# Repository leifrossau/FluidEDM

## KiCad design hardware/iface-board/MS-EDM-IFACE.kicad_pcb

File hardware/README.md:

# Microspark EDM — Hardware (KiCad 10)

KiCad 10 projects for the two boards the firmware talks to over CAN-FD but that did not yet
exist: the **dielectric (coolant) controller** and the **EDM pulse supply (PSU)**. Both were
generated programmatically with KiCad 10's headless `pcbnew` Python API + `kicad-cli`.

> **These are AI-generated first-pass designs, NOT fabrication-ready.** Read each board's
> `DESIGN.md` (every significant choice is flagged **[REVIEW]**). The PSU board is high-voltage
> and **must not be fabricated or powered without a qualified power-electronics review,
> simulation, and staged bench bring-up** — see `psu-board/DESIGN.md`.

## Layout
```
hardware/
  dielectric-module/   MS-DIEL-CTRL — ESP32-S3 + MCP2518FD CAN node, coolant sensors/drives
  psu-board/           MS-EDM-PSU   — STM32G474 HV pulse generator + classifier (review-only)
  lib/                 (project-local symbols/footprints, if any)
  scripts/kizen.py     shared headless board-builder helper
```
Each board dir has: `DESIGN.md` (the engineering), `generate_board.py` (regenerates the PCB),
`*.kicad_pro/.kicad_pcb` (the KiCad project — open in **KiCad 10**, not 9), `*.netlist.csv`
(pad→net review table), `*.bom.csv`, and `*.placement.pdf` (a rendered view).

## Workflow: schematic-first (linked)
The **dielectric board** is generated schematic-first (option A): one shared source model
(`generate.py`, the `PARTS` + `NETS` tables) emits BOTH the `.kicad_sch` (source of truth)
and the `.kicad_pcb`, with each footprint carrying the **same UUID** as its schematic symbol —
so the two are linked and "Update PCB from Schematic" / ERC are meaningful. ICs are wired by
**pin name** resolved against the real library symbol (authoritative pinouts, e.g. MCP2518FD
SCK=10/SDI=11/SDO=12/CS=13), the ESP32 by GPIO name. Connectivity in the schematic is
**global-label-per-pin** — ERC-valid and netlist-correct, but a flat "label wall", not a
hand-drawn schematic; prettify wiring in eeschema if desired. The toolkit is `scripts/kisch.py`
(schematic) + `scripts/kizen.py` (PCB). The **PSU board** is still the earlier PCB-only scaffold.

## What is done vs. what's left
**Done (autonomously):** architecture + part selection, a **linked schematic + PCB** (dielectric),
real-symbol pinouts, board outline, block placement, complete netlist/ratsnest, copper-pour
outlines, mounting, ERC + DRC + schematic/PCB PDFs, BOM.

**Left (needs the KiCad GUI / a human):**
- **Routing** — nothing is routed (the ratsnest shows all connections). DRC's "unconnected" count is expected.
- **ERC nags** — the generated schematic leaves benign warnings: unused-GPIO `pin_not_connected`
  (add no-connect flags), `power_pin_not_driven` (add `PWR_FLAG`s), and `lib_symbol_mismatch`
  (the embedded symbols differ slightly from the library cache — "Update Symbols from Library").
- **Placement polish** — remaining DRC items are mostly silkscreen-label overlaps + courtyard
  nudges + default drill-rule flags on the big mount/terminal holes; resolve while routing.
- **A few [REVIEW] part choices** — buck `AP3402`, reverse-FET `AO3401A`, and the programming
  header replacing USB-C (pad-mapping); confirm against the BOM you intend to buy.
- **Pour fill** — zones are left unfilled (headless `ZONE_FILLER` segfaults); press **B** in pcbnew.

## Regenerate a board
```powershell
& "C:\Program Files\KiCad\10.0\bin\python.exe" hardware\dielectric-module\generate.py        # schematic + linked PCB
& "C:\Program Files\KiCad\10.0\bin\python.exe" hardware\psu-board\generate_board.py           # PCB scaffold only
```
Render / check (kicad-cli):
```powershell
$cli = "C:\Program Files\KiCad\10.0\bin\kicad-cli.exe"
& $cli pcb export pdf  --layers "F.Cu,F.Silkscreen,F.Fab,Edge.Cuts" --mode-single <board>.kicad_pcb
& $cli pcb drc --format json --output drc.json <board>.kicad_pcb
```
The generators are **idempotent** — re-running rebuilds the `.kicad_pcb` from the component +
net tables in `generate_board.py`. Edit those tables (or `scripts/kizen.py`) to change the board;
re-run to regenerate. (Once you start hand-editing/routing in the GUI, stop re-running the
generator or it will overwrite your work — at that point the `.kicad_pcb` is the source of truth.)

## Firmware contracts these implement
- **Dielectric:** CAN IDs `0x710–0x740` — `docs/superpowers/specs/2026-06-14-dielectric-module-design.md`.
- **PSU:** CAN IDs `0x010/0x020/0x100/0x300` — the PSU integration design spec.
Both boards' MCUs run separate firmware (not in this repo yet); the contracts + the firmware's
`SimPsuLink`/`SimDielLink` simulators let you validate the bus handshake before either board exists.

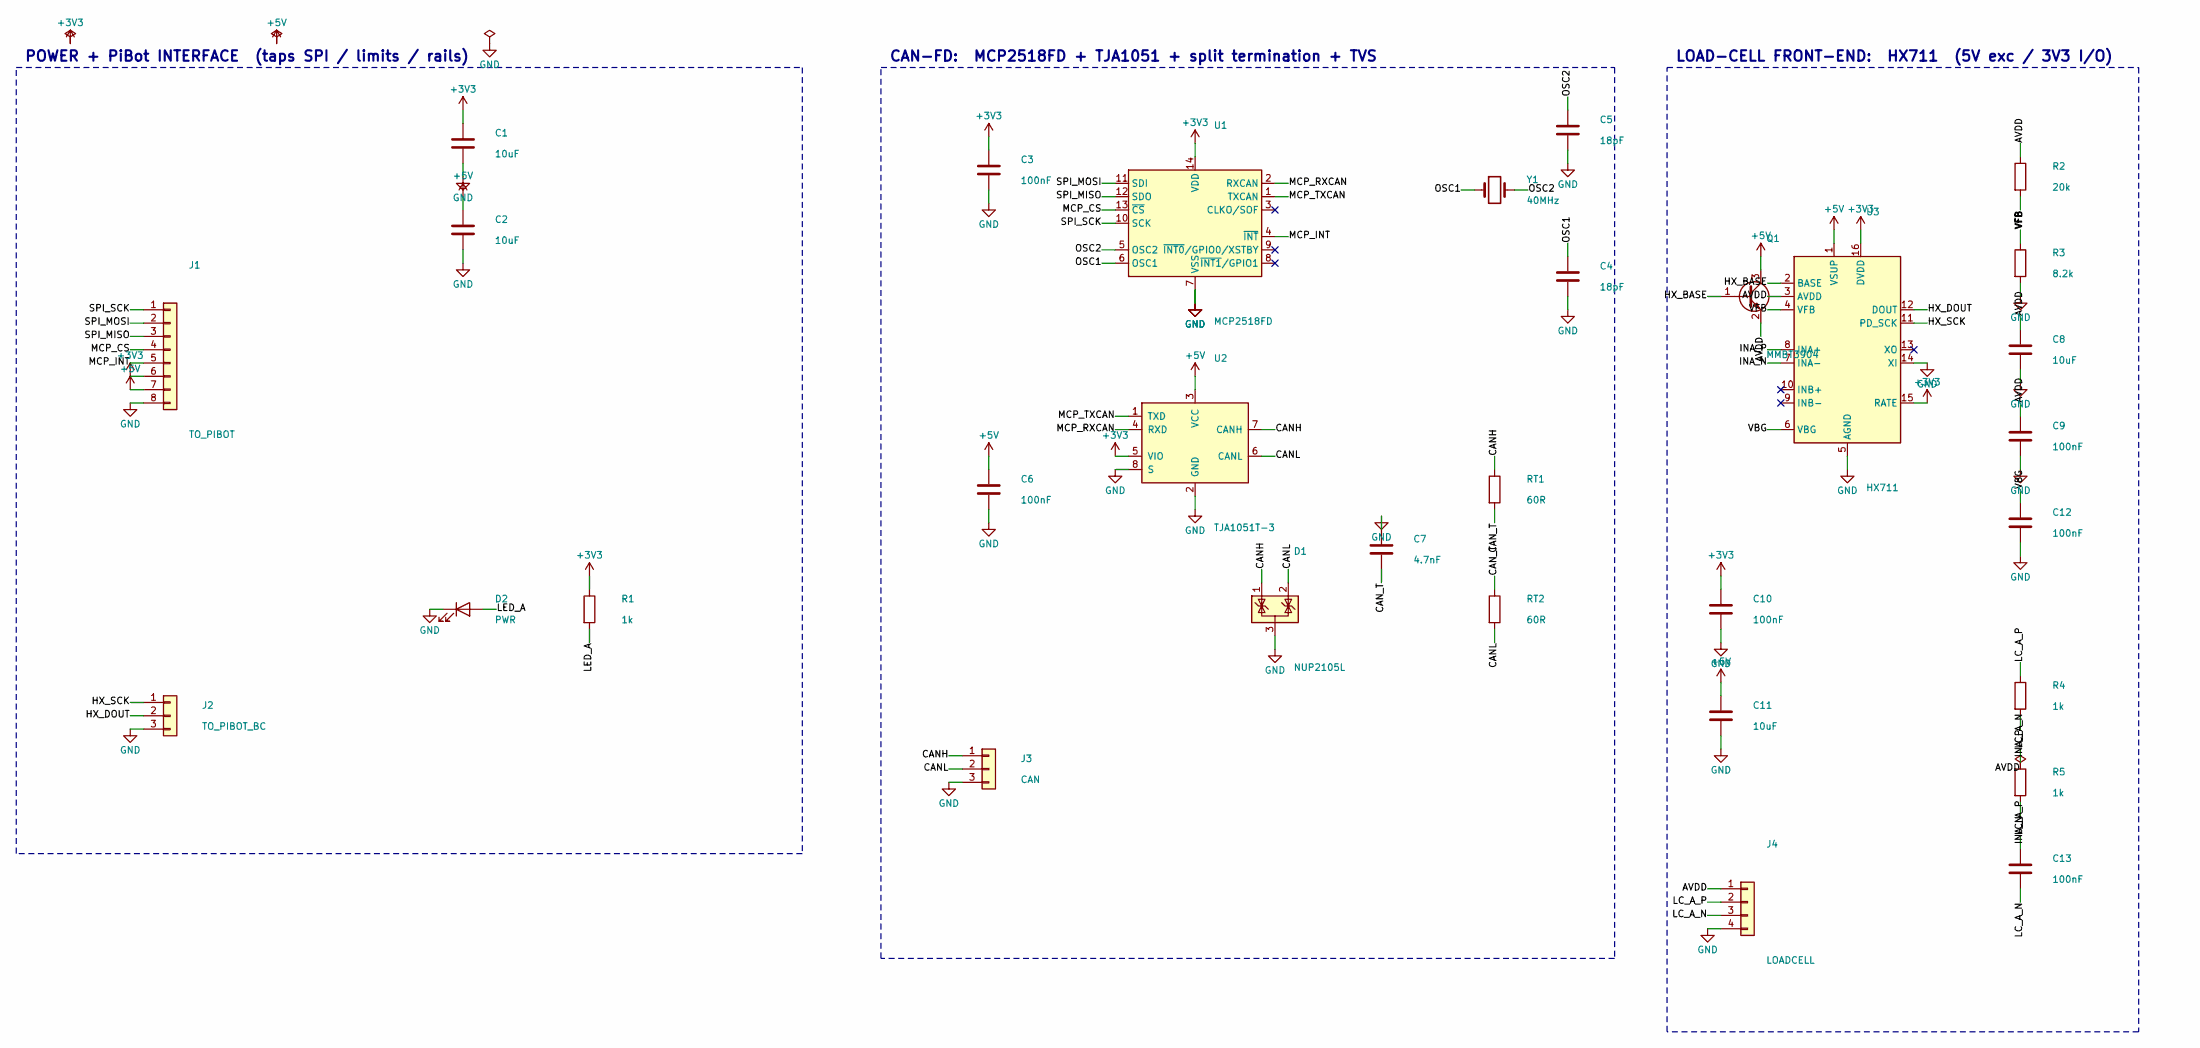
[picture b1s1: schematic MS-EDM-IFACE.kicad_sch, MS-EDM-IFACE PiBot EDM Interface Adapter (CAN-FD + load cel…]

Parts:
C1, C2, C8, C11: 10uF; C_0805_2012Metric
C3, C6, C9, C10, C12, C13: 100nF; C_0805_2012Metric
C4, C5: 18pF; C_0805_2012Metric
C7: 4.7nF; C_0805_2012Metric
D1: NUP2105L; SOT-23
D2: PWR; LED_0805_2012Metric
J1: TO_PIBOT; PinHeader_1x08_P2.54mm_Vertical
J2: TO_PIBOT_BC; PinHeader_1x03_P2.54mm_Vertical
J3: CAN; TerminalBlock_Phoenix_MPT-0,5-3-2.54_1x03_P2.54mm_Horizontal
J4: LOADCELL; JST_XH_B4B-XH-A_1x04_P2.50mm_Vertical
Q1: MMBT3904; SOT-23
R1, R4, R5: 1k; R_0805_2012Metric
R2: 20k; R_0805_2012Metric
R3: 8.2k; R_0805_2012Metric
RT1, RT2: 60R; R_0805_2012Metric
U1: MCP2518FD; SOIC-14_3.9x8.7mm_P1.27mm
U2: TJA1051T-3; SOIC-8_3.9x4.9mm_P1.27mm
U3: HX711; SOIC-16_3.9x9.9mm_P1.27mm
Y1: 40MHz; Crystal_SMD_3215-2Pin_3.2x1.5mm

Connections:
+3V3: C1.1, C3.1, C10.1, J1.6, R1.1, U1.14 (VDD), U2.5 (VIO), U3.15 (RATE), U3.16 (DVDD)
+5V: C2.1, C6.1, C11.1, J1.7, Q1.3 (C), U2.3 (VCC), U3.1 (VSUP)
AVDD: C8.1, C9.1, J4.1, Q1.2 (E), R2.1, U3.3 (AVDD)
CANH: D1.1 (K), J3.1, RT1.1, U2.7 (CANH)
CANL: D1.2 (K), J3.2, RT2.2, U2.6 (CANL)
CAN_T: C7.2, RT1.2, RT2.1
GND: C1.2, C2.2, C3.2, C4.2, C5.2, C6.2, C7.1, C8.2, C9.2, C10.2, C11.2, C12.2, D1.3 (A), D2.1 (K), J1.8, J2.3, J3.3, J4.4, R3.2, U1.7 (VSS), U1.15 (VSS), U2.2 (GND), U2.8 (S), U3.5 (AGND), U3.14 (XI)
HX_BASE: Q1.1 (B), U3.2 (BASE)
HX_DOUT: J2.2, U3.12 (DOUT)
HX_SCK: J2.1, U3.11 (PD_SCK)
INA_N: R5.2, U3.7 (INA-)
INA_P: R4.2, U3.8 (INA+)
LC_A_N: C13.2, J4.3, R5.1
LC_A_P: C13.1, J4.2, R4.1
LED_A: D2.2 (A), R1.2
MCP_CS: J1.4, U1.13 (~CS)
MCP_INT: J1.5, U1.4 (~INT)
MCP_RXCAN: U1.2 (RXCAN), U2.4 (RXD)
MCP_TXCAN: U1.1 (TXCAN), U2.1 (TXD)
OSC1: C4.1, U1.6 (OSC1), Y1.1
OSC2: C5.1, U1.5 (OSC2), Y1.2
SPI_MISO: J1.3, U1.12 (SDO)
SPI_MOSI: J1.2, U1.11 (SDI)
SPI_SCK: J1.1, U1.10 (SCK)
VBG: C12.1, U3.6 (VBG)
VFB: R2.2, R3.1, U3.4 (VFB)

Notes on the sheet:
POWER + PiBot INTERFACE (taps SPI / limits / rails)
CAN-FD: MCP2518FD + TJA1051 + split termination + TVS
LOAD-CELL FRONT-END: HX711 (5V exc / 3V3 I/O)

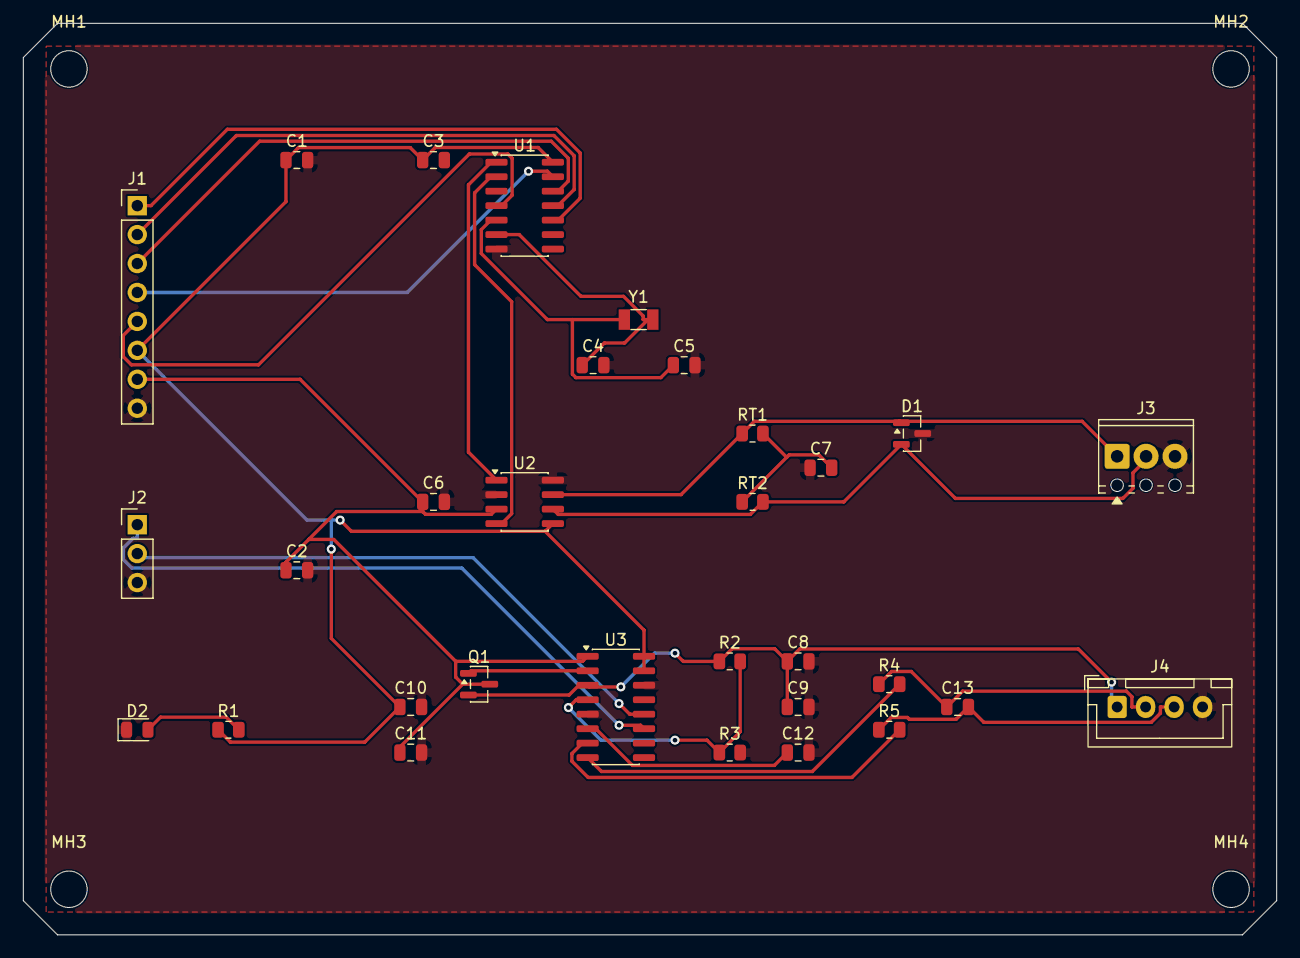
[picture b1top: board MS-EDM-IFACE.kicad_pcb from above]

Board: 2 copper layers, 110.0 x 80.0 mm, 35 parts (0 on the bottom side), 26 nets.

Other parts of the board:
MH1, MH2, MH3, MH4: M3; MountingHole_3.2mm_M3

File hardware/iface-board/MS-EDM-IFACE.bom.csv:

qty,value,footprint,refs
6,100nF,C_0805_2012Metric,C10 C12 C13 C3 C6 C9
4,10uF,C_0805_2012Metric,C1 C11 C2 C8
2,18pF,C_0805_2012Metric,C4 C5
3,1k,R_0805_2012Metric,R1 R4 R5
1,20k,R_0805_2012Metric,R2
1,4.7nF,C_0805_2012Metric,C7
1,40MHz,Crystal_SMD_3215-2Pin_3.2x1.5mm,Y1
2,60R,R_0805_2012Metric,RT1 RT2
1,8.2k,R_0805_2012Metric,R3
1,CAN,"TerminalBlock_Phoenix_MPT-0,5-3-2.54_1x03_P2.54mm_Horizontal",J3
1,HX711,SOIC-16_3.9x9.9mm_P1.27mm,U3
1,LOADCELL,JST_XH_B4B-XH-A_1x04_P2.50mm_Vertical,J4
4,M3,MountingHole_3.2mm_M3,MH1 MH2 MH3 MH4
1,MCP2518FD,SOIC-14_3.9x8.7mm_P1.27mm,U1
1,MMBT3904,SOT-23,Q1
1,NUP2105L,SOT-23,D1
1,PWR,LED_0805_2012Metric,D2
1,TJA1051T-3,SOIC-8_3.9x4.9mm_P1.27mm,U2
1,TO_PIBOT,PinHeader_1x08_P2.54mm_Vertical,J1
1,TO_PIBOT_BC,PinHeader_1x03_P2.54mm_Vertical,J2

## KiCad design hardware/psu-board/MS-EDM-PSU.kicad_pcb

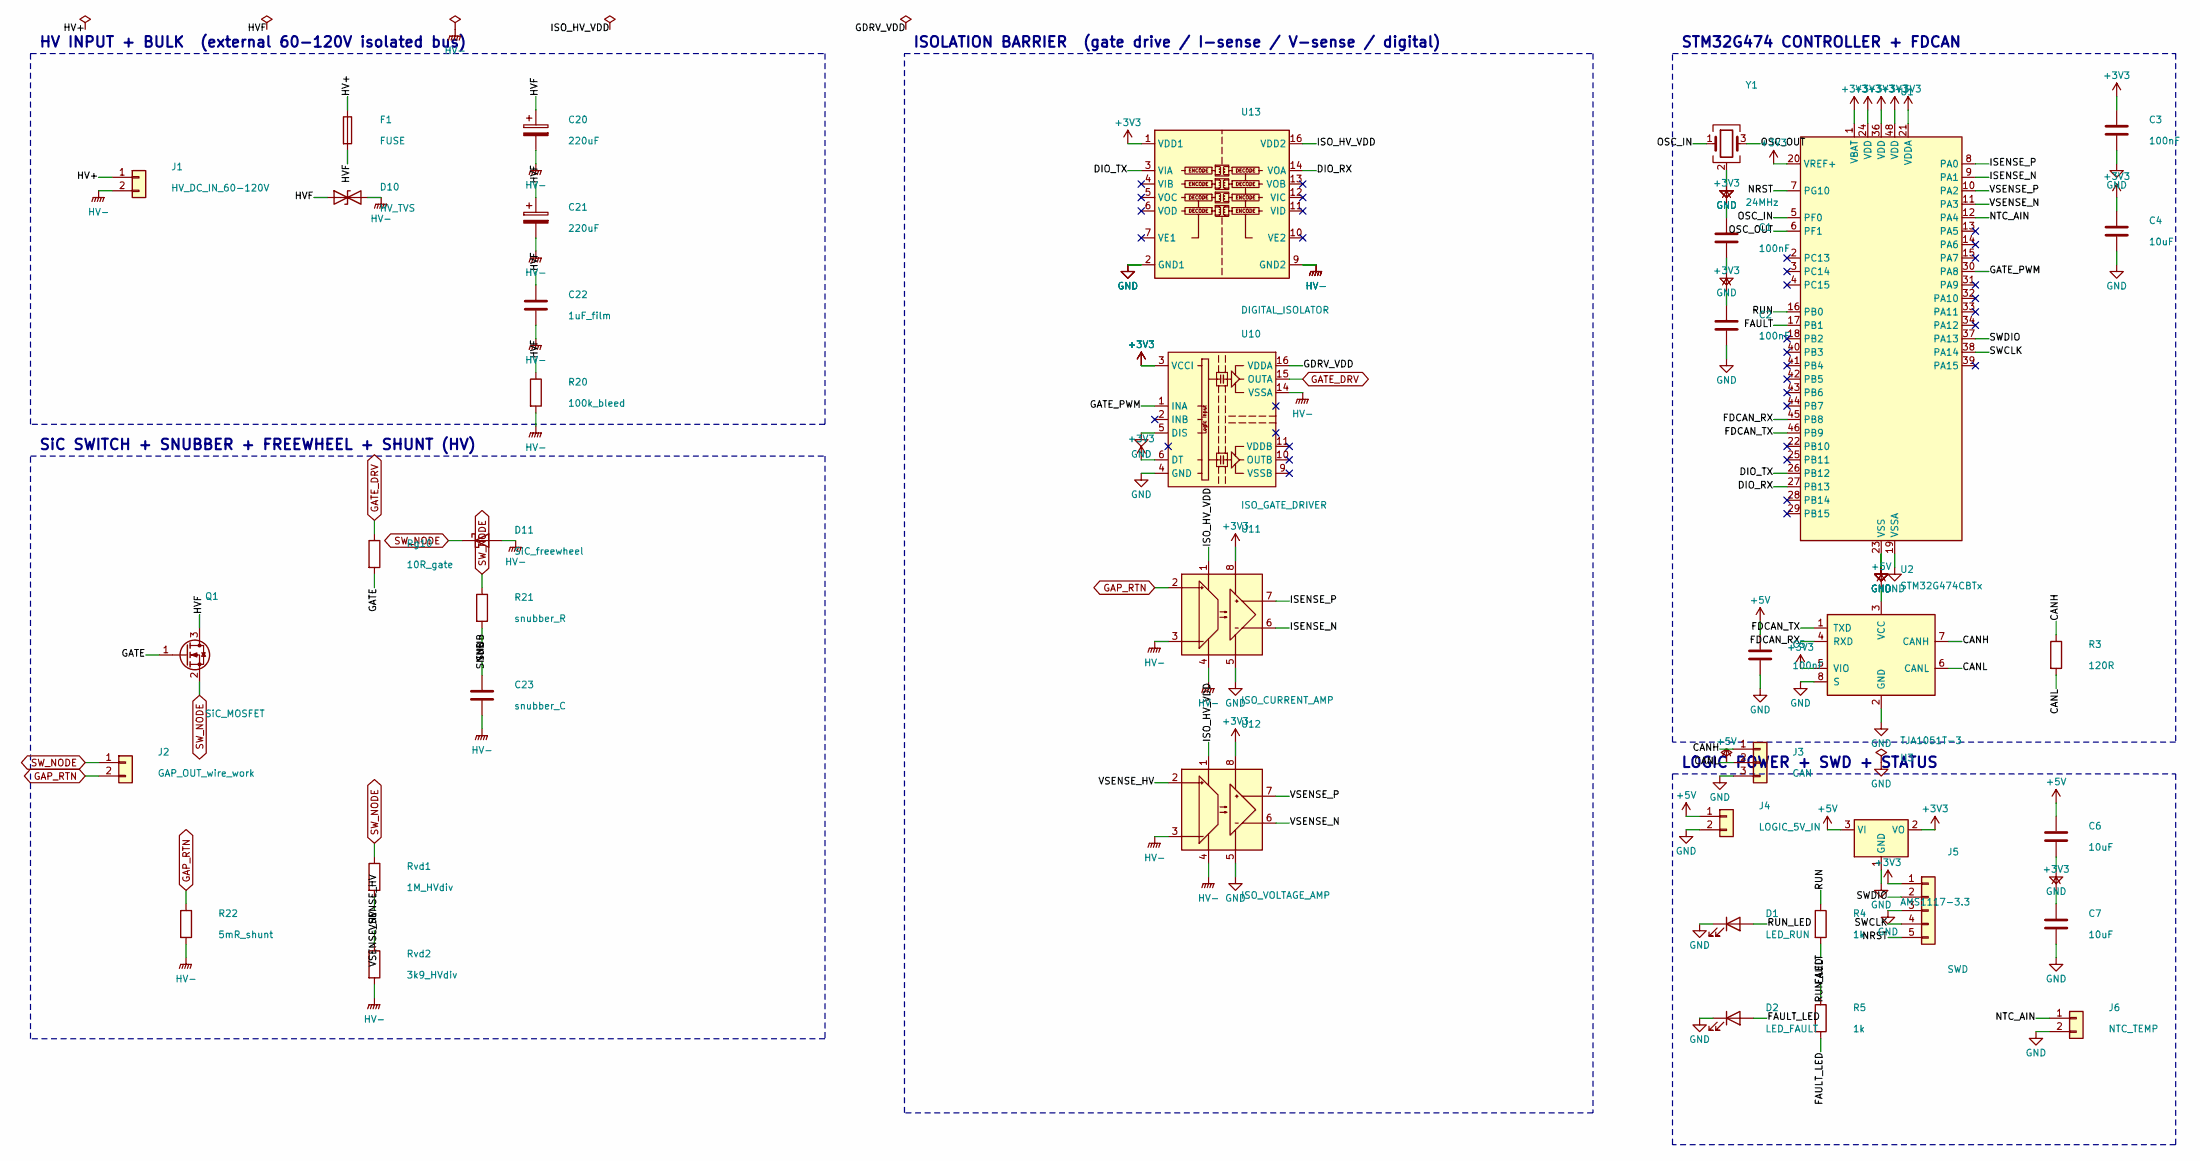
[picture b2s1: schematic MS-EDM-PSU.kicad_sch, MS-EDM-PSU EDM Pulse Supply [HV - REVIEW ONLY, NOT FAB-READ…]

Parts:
C1, C2, C3, C5: 100nF; C_0805_2012Metric
C4, C6, C7: 10uF; C_0805_2012Metric
C20, C21: 220uF; CP_Radial_D10.0mm_P5.00mm
C22: 1uF_film; C_1210_3225Metric
C23: snubber_C; C_0805_2012Metric
D1: LED_RUN; LED_0805_2012Metric
D2: LED_FAULT; LED_0805_2012Metric
D10: HV_TVS; D_SMC
D11: SiC_freewheel; D_SMC
F1: FUSE; R_2512_6332Metric
J1: HV_DC_IN_60-120V; TerminalBlock_Phoenix_MPT-0,5-2-2.54_1x02_P2.54mm_Horizontal
J2: GAP_OUT_wire_work; TerminalBlock_Phoenix_MPT-0,5-2-2.54_1x02_P2.54mm_Horizontal
J3: CAN; TerminalBlock_Phoenix_MPT-0,5-3-2.54_1x03_P2.54mm_Horizontal
J4: LOGIC_5V_IN; TerminalBlock_Phoenix_MPT-0,5-2-2.54_1x02_P2.54mm_Horizontal
J5: SWD; PinHeader_1x05_P2.54mm_Vertical
J6: NTC_TEMP; TerminalBlock_Phoenix_MPT-0,5-2-2.54_1x02_P2.54mm_Horizontal
Q1: SiC_MOSFET; TO-247-3_Vertical
R3: 120R; R_0805_2012Metric
R4, R5: 1k; R_0805_2012Metric
R20: 100k_bleed; R_2512_6332Metric
R21: snubber_R; R_2512_6332Metric
R22: 5mR_shunt; R_2512_6332Metric
Rg10: 10R_gate; R_0805_2012Metric
Rvd1: 1M_HVdiv; R_2512_6332Metric
Rvd2: 3k9_HVdiv; R_0805_2012Metric
U1: STM32G474CBTx; LQFP-48_7x7mm_P0.5mm
U2: TJA1051T-3; SOIC-8_3.9x4.9mm_P1.27mm
U3: AMS1117-3.3; SOT-223-3_TabPin2
U10: ISO_GATE_DRIVER; SOIC-16W_7.5x10.3mm_P1.27mm
U11: ISO_CURRENT_AMP; SOIC-8_3.9x4.9mm_P1.27mm
U12: ISO_VOLTAGE_AMP; SOIC-8_3.9x4.9mm_P1.27mm
U13: DIGITAL_ISOLATOR; SOIC-16_3.9x9.9mm_P1.27mm
Y1: 24MHz; Crystal_SMD_3225-4Pin_3.2x2.5mm

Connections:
+3V3: C1.1, C2.1, C3.1, C4.1, C7.1, J5.1, U1.1 (VBAT), U1.20 (VREF+), U1.21 (VDDA), U1.24 (VDD), U1.36 (VDD), U1.48 (VDD), U2.5 (VIO), U3.2 (VO), U10.3 (VCCI), U10.6 (DT), U10.8 (VCCI), U11.8 (VDD2), U12.8 (VDD2), U13.1 (VDD1)
CANH: J3.1, R3.1, U2.7 (CANH)
DIO_RX: U1.27 (PB13), U13.14 (VOA)
DIO_TX: U1.26 (PB12), U13.3 (VIA)
FAULT: R5.1, U1.17 (PB1)
FAULT_LED: D2.2 (A), R5.2
FDCAN_RX: U1.45 (PB8), U2.4 (RXD)
FDCAN_TX: U1.46 (PB9), U2.1 (TXD)
GAP_RTN: J2.2, R22.1, U11.2 (VINP)
GATE: Q1.1 (G), Rg10.2
GATE_DRV: Rg10.1, U10.15 (OUTA)
GATE_PWM: U1.30 (PA8), U10.1 (INA)
GDRV_VDD: U10.16 (VDDA)
GND: C1.2, C2.2, C3.2, C4.2, C5.2, C6.2, C7.2, D1.1 (K), D2.1 (K), J3.3, J4.2, J5.3, J6.2, U1.19 (VSSA), U1.23 (VSS), U1.35 (VSS), U1.47 (VSS), U2.2 (GND), U2.8 (S), U3.1 (GND), U10.4 (GND), U10.5 (DIS), U11.5 (GND2), U12.5 (GND2), U13.2 (GND1), U13.8 (GND1), Y1.2 (G), Y1.4 (G)
HV+: F1.1, J1.1
HV-: C20.2, C21.2, C22.2, C23.2, D10.2 (A2), D11.2 (A), J1.2, R20.2, R22.2, Rvd2.2, U10.14 (VSSA), U11.3 (VINN), U11.4 (GND1), U12.3 (VINN), U12.4 (GND1), U13.9 (GND2), U13.15 (GND2)
HVF: C20.1, C21.1, C22.1, D10.1 (A1), F1.2, Q1.3 (D), R20.1
ISENSE_N: U1.9 (PA1), U11.6 (VOUTN)
ISENSE_P: U1.8 (PA0), U11.7 (VOUTP)
ISO_HV_VDD: U11.1 (VDD1), U12.1 (VDD1), U13.16 (VDD2)
NRST: J5.5, U1.7 (PG10)
NTC_AIN: J6.1, U1.12 (PA4)
OSC_IN: U1.5 (PF0), Y1.1
OSC_OUT: U1.6 (PF1), Y1.3
RUN: R4.1, U1.16 (PB0)
RUN_LED: D1.2 (A), R4.2
SNUB: C23.1, R21.2
SWCLK: J5.4, U1.38 (PA14)
SWDIO: J5.2, U1.37 (PA13)
SW_NODE: D11.1 (K), J2.1, Q1.2 (S), R21.1, Rvd1.1
VSENSE_HV: Rvd1.2, Rvd2.1, U12.2 (VINP)
VSENSE_N: U1.11 (PA3), U12.6 (VOUTN)
VSENSE_P: U1.10 (PA2), U12.7 (VOUTP)

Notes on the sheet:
HV INPUT + BULK (external 60-120V isolated bus)
SiC SWITCH + SNUBBER + FREEWHEEL + SHUNT (HV)
ISOLATION BARRIER (gate drive / I-sense / V-sense / digital)
STM32G474 CONTROLLER + FDCAN
LOGIC POWER + SWD + STATUS

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
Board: 4 copper layers, 44 parts (0 on the bottom side), 34 nets, no tracks yet.

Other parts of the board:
MH1, MH2, MH3, MH4: M3; MountingHole_3.2mm_M3

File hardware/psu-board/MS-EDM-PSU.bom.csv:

qty,value,footprint,refs
1,100k_bleed,R_2512_6332Metric,R20
4,100nF,C_0805_2012Metric,C1 C2 C3 C5
1,10R_gate,R_0805_2012Metric,Rg10
3,10uF,C_0805_2012Metric,C4 C6 C7
1,120R,R_0805_2012Metric,R3
1,1M_HVdiv,R_2512_6332Metric,Rvd1
2,1k,R_0805_2012Metric,R4 R5
1,1uF_film,C_1210_3225Metric,C22
2,220uF,CP_Radial_D10.0mm_P5.00mm,C20 C21
1,24MHz,Crystal_SMD_3225-4Pin_3.2x2.5mm,Y1
1,3k9_HVdiv,R_0805_2012Metric,Rvd2
1,5mR_shunt,R_2512_6332Metric,R22
1,AMS1117-3.3,SOT-223-3_TabPin2,U3
1,CAN,"TerminalBlock_Phoenix_MPT-0,5-3-2.54_1x03_P2.54mm_Horizontal",J3
1,DIGITAL_ISOLATOR,SOIC-16_3.9x9.9mm_P1.27mm,U13
1,FUSE,R_2512_6332Metric,F1
1,GAP_OUT_wire_work,"TerminalBlock_Phoenix_MPT-0,5-2-2.54_1x02_P2.54mm_Horizontal",J2
1,HV_DC_IN_60-120V,"TerminalBlock_Phoenix_MPT-0,5-2-2.54_1x02_P2.54mm_Horizontal",J1
1,HV_TVS,D_SMC,D10
1,ISO_CURRENT_AMP,SOIC-8_3.9x4.9mm_P1.27mm,U11
1,ISO_GATE_DRIVER,SOIC-16W_7.5x10.3mm_P1.27mm,U10
1,ISO_VOLTAGE_AMP,SOIC-8_3.9x4.9mm_P1.27mm,U12
1,LED_FAULT,LED_0805_2012Metric,D2
1,LED_RUN,LED_0805_2012Metric,D1
1,LOGIC_5V_IN,"TerminalBlock_Phoenix_MPT-0,5-2-2.54_1x02_P2.54mm_Horizontal",J4
4,M3,MountingHole_3.2mm_M3,MH1 MH2 MH3 MH4
1,NTC_TEMP,"TerminalBlock_Phoenix_MPT-0,5-2-2.54_1x02_P2.54mm_Horizontal",J6
1,STM32G474CBTx,LQFP-48_7x7mm_P0.5mm,U1
1,SWD,PinHeader_1x05_P2.54mm_Vertical,J5
1,SiC_MOSFET,TO-247-3_Vertical,Q1
1,SiC_freewheel,D_SMC,D11
1,TJA1051T-3,SOIC-8_3.9x4.9mm_P1.27mm,U2
1,snubber_C,C_0805_2012Metric,C23
1,snubber_R,R_2512_6332Metric,R21

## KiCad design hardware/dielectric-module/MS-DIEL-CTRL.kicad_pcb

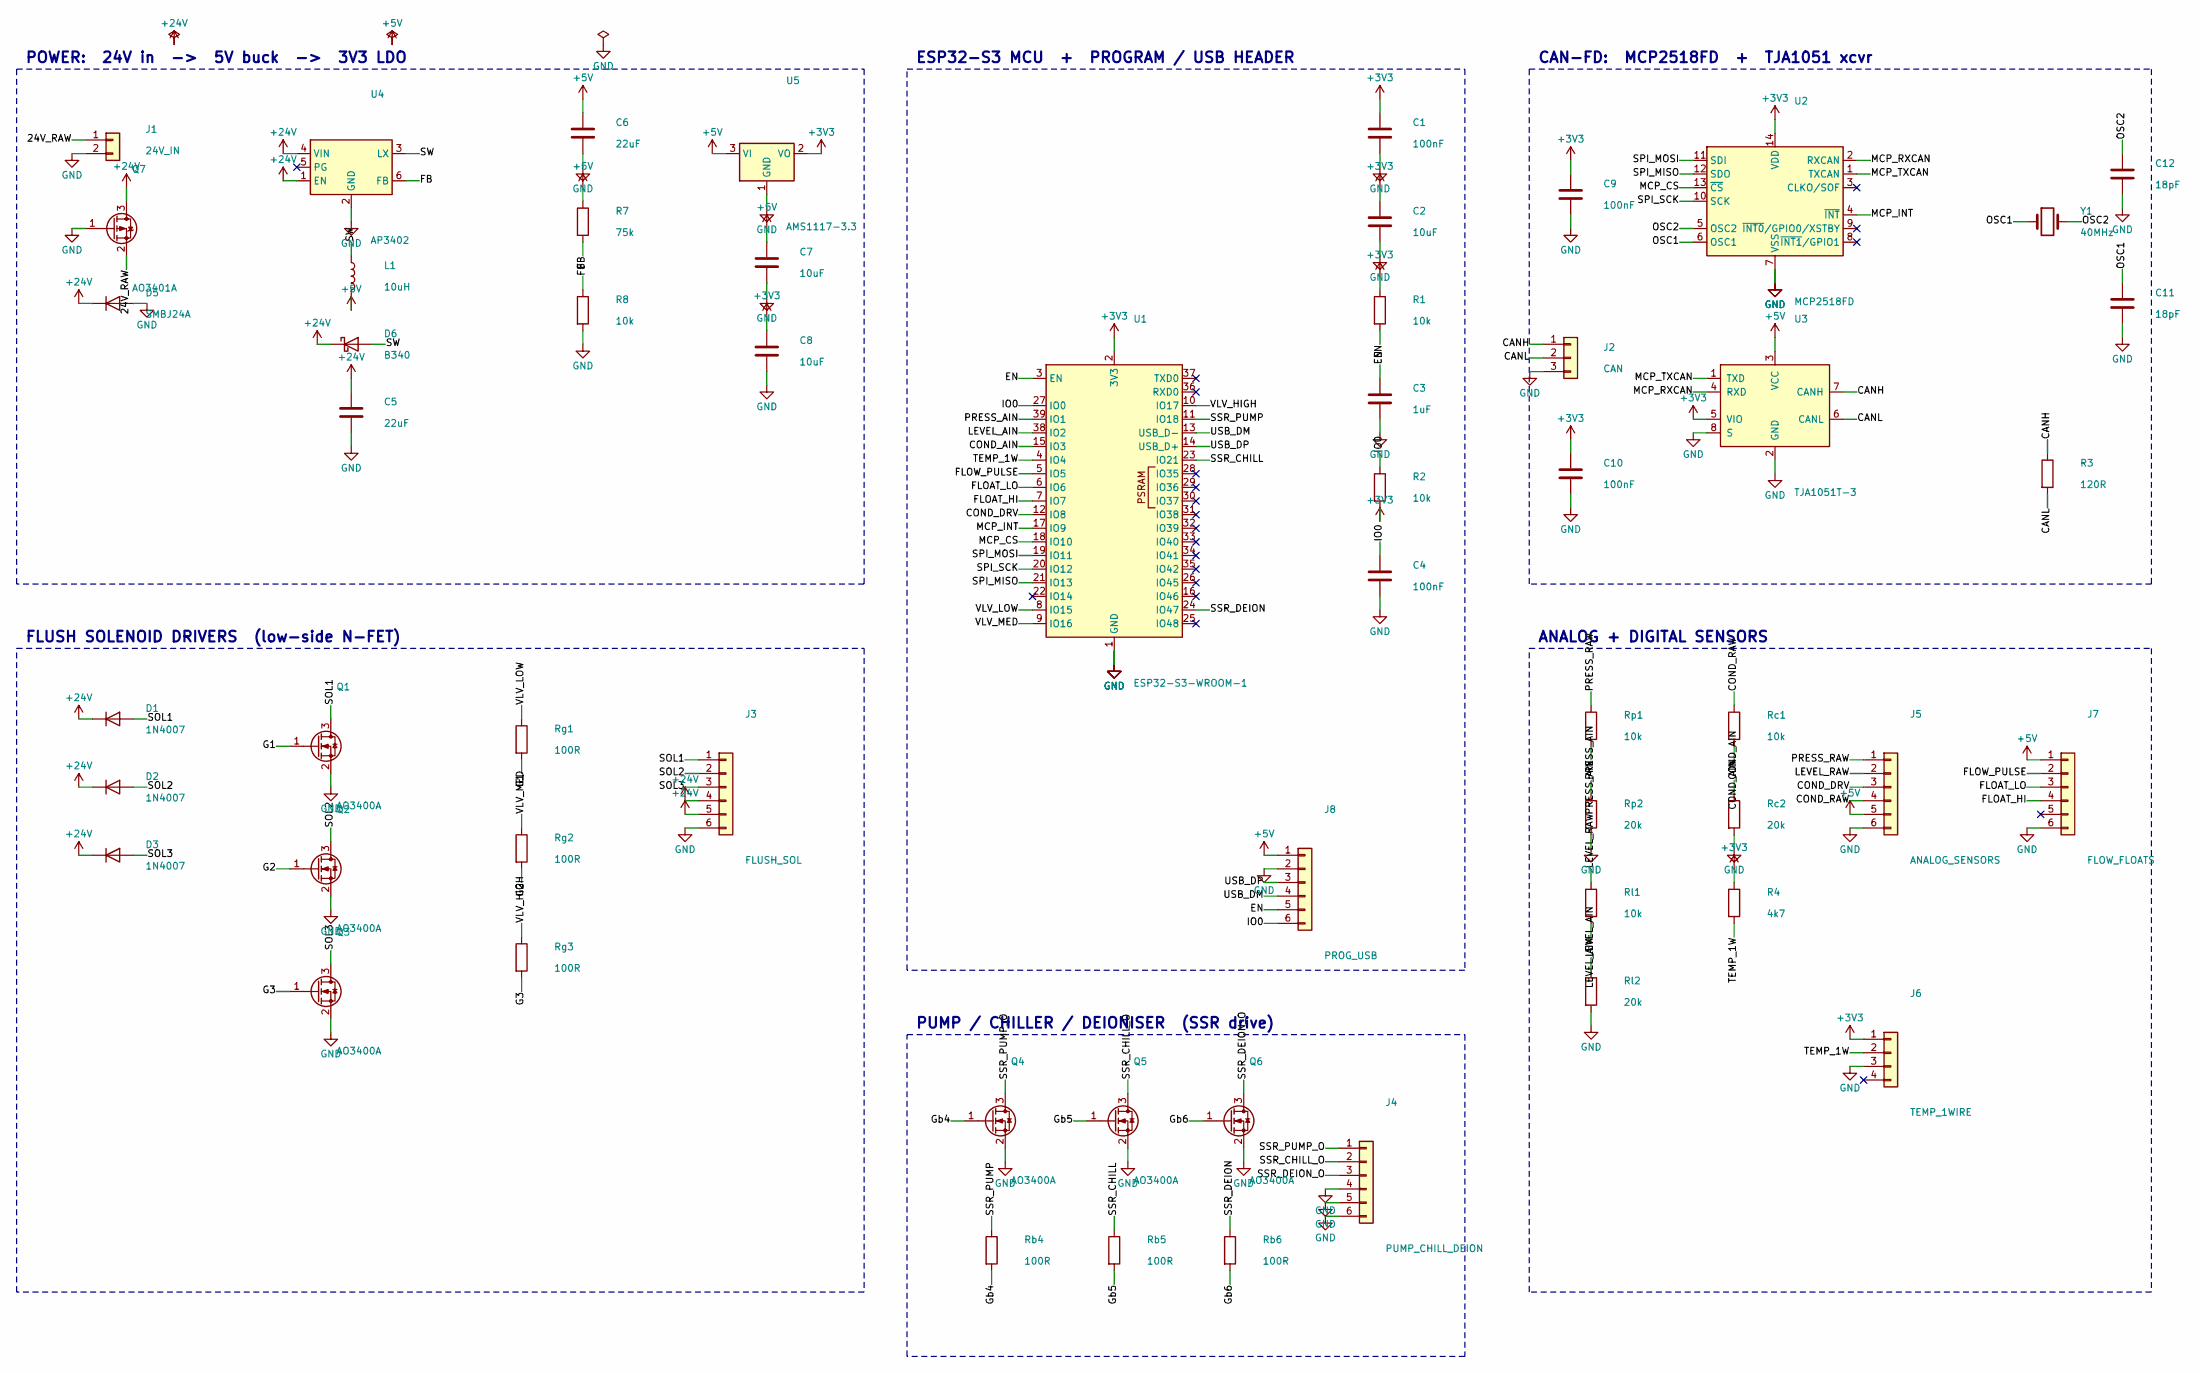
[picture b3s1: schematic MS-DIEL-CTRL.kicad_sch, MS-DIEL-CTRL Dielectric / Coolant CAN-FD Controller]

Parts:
C1, C4, C9, C10: 100nF; C_0805_2012Metric
C2, C7, C8: 10uF; C_0805_2012Metric
C3: 1uF; C_0805_2012Metric
C5, C6: 22uF; C_0805_2012Metric
C11, C12: 18pF; C_0805_2012Metric
D1, D2, D3: 1N4007; D_SMA
D5: SMBJ24A; D_SMA
D6: B340; D_SMA
J1: 24V_IN; TerminalBlock_Phoenix_MPT-0,5-2-2.54_1x02_P2.54mm_Horizontal
J2: CAN; TerminalBlock_Phoenix_MPT-0,5-3-2.54_1x03_P2.54mm_Horizontal
J3: FLUSH_SOL; TerminalBlock_Phoenix_MPT-0,5-6-2.54_1x06_P2.54mm_Horizontal
J4: PUMP_CHILL_DEION; TerminalBlock_Phoenix_MPT-0,5-6-2.54_1x06_P2.54mm_Horizontal
J5: ANALOG_SENSORS; JST_XH_B6B-XH-A_1x06_P2.50mm_Vertical
J6: TEMP_1WIRE; JST_XH_B4B-XH-A_1x04_P2.50mm_Vertical
J7: FLOW_FLOATS; JST_XH_B6B-XH-A_1x06_P2.50mm_Vertical
J8: PROG_USB; PinHeader_1x06_P2.54mm_Vertical
L1: 10uH; L_7.3x7.3_H3.5
Q1, Q2, Q3, Q4, Q5, Q6: AO3400A; SOT-23
Q7: AO3401A; SOT-23
R1, R2, R8: 10k; R_0805_2012Metric
R3: 120R; R_0805_2012Metric
R4: 4k7; R_0805_2012Metric
R7: 75k; R_0805_2012Metric
Rb4, Rb5, Rb6: 100R; R_0805_2012Metric
Rc1: 10k; R_0805_2012Metric
Rc2: 20k; R_0805_2012Metric
Rg1, Rg2, Rg3: 100R; R_0805_2012Metric
Rl1: 10k; R_0805_2012Metric
Rl2: 20k; R_0805_2012Metric
Rp1: 10k; R_0805_2012Metric
Rp2: 20k; R_0805_2012Metric
U1: ESP32-S3-WROOM-1
U2: MCP2518FD; SOIC-14_3.9x8.7mm_P1.27mm
U3: TJA1051T-3; SOIC-8_3.9x4.9mm_P1.27mm
U4: AP3402; SOT-23-6
U5: AMS1117-3.3; SOT-223-3_TabPin2
Y1: 40MHz; Crystal_SMD_3215-2Pin_3.2x1.5mm

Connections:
24V_RAW: J1.1, Q7.2 (S)
+3V3: C1.1, C2.1, C8.1, C9.1, C10.1, J6.1, R1.1, R2.2, R4.1, U1.2 (3V3), U2.14 (VDD), U3.5 (VIO), U5.2 (VO)
+5V: C6.1, C7.1, J5.5, J7.1, J8.1, L1.2, R7.1, U3.3 (VCC), U5.3 (VI)
+24V: C5.1, D1.1 (K), D2.1 (K), D3.1 (K), D5.1 (K), D6.1 (K), J3.4, J3.5, Q7.3 (D), U4.1 (EN), U4.4 (VIN)
CANH: J2.1, R3.1, U3.7 (CANH)
CANL: J2.2, R3.2, U3.6 (CANL)
COND_AIN: Rc1.2, Rc2.1, U1.15 (IO3)
COND_DRV: J5.3, U1.12 (IO8)
COND_RAW: J5.4, Rc1.1
EN: C3.1, J8.5, R1.2, U1.3 (EN)
FB: R7.2, R8.1, U4.6 (FB)
FLOAT_HI: J7.4, U1.7 (IO7)
FLOAT_LO: J7.3, U1.6 (IO6)
FLOW_PULSE: J7.2, U1.5 (IO5)
G1: Q1.1 (G), Rg1.2
G2: Q2.1 (G), Rg2.2
G3: Q3.1 (G), Rg3.2
GND: C1.2, C2.2, C3.2, C4.2, C5.2, C6.2, C7.2, C8.2, C9.2, C10.2, C11.2, C12.2, D5.2 (A), J1.2, J2.3, J3.6, J4.4, J4.5, J4.6, J5.6, J6.3, J7.6, J8.2, Q1.2 (S), Q2.2 (S), Q3.2 (S), Q4.2 (S), Q5.2 (S), Q6.2 (S), Q7.1 (G), R8.2, Rc2.2, Rl2.2, Rp2.2, U1.1 (GND), U1.40 (GND), U1.41 (GND), U2.7 (VSS), U2.15 (VSS), U3.2 (GND), U3.8 (S), U4.2 (GND), U5.1 (GND)
Gb4: Q4.1 (G), Rb4.2
Gb5: Q5.1 (G), Rb5.2
Gb6: Q6.1 (G), Rb6.2
IO0: C4.1, J8.6, R2.1, U1.27 (IO0)
LEVEL_AIN: Rl1.2, Rl2.1, U1.38 (IO2)
LEVEL_RAW: J5.2, Rl1.1
MCP_CS: U1.18 (IO10), U2.13 (~CS)
MCP_INT: U1.17 (IO9), U2.4 (~INT)
MCP_RXCAN: U2.2 (RXCAN), U3.4 (RXD)
MCP_TXCAN: U2.1 (TXCAN), U3.1 (TXD)
OSC1: C11.1, U2.6 (OSC1), Y1.1
OSC2: C12.1, U2.5 (OSC2), Y1.2
PRESS_AIN: Rp1.2, Rp2.1, U1.39 (IO1)
PRESS_RAW: J5.1, Rp1.1
SOL1: D1.2 (A), J3.1, Q1.3 (D)
SOL2: D2.2 (A), J3.2, Q2.3 (D)
SOL3: D3.2 (A), J3.3, Q3.3 (D)
SPI_MISO: U1.21 (IO13), U2.12 (SDO)
SPI_MOSI: U1.19 (IO11), U2.11 (SDI)
SPI_SCK: U1.20 (IO12), U2.10 (SCK)
SSR_CHILL: Rb5.1, U1.23 (IO21)
SSR_CHILL_O: J4.2, Q5.3 (D)
SSR_DEION: Rb6.1, U1.24 (IO47)
SSR_DEION_O: J4.3, Q6.3 (D)
SSR_PUMP: Rb4.1, U1.11 (IO18)
SSR_PUMP_O: J4.1, Q4.3 (D)
SW: D6.2 (A), L1.1, U4.3 (LX)
TEMP_1W: J6.2, R4.2, U1.4 (IO4)
USB_DM: J8.4, U1.13 (USB_D-)
USB_DP: J8.3, U1.14 (USB_D+)
VLV_HIGH: Rg3.1, U1.10 (IO17)
VLV_LOW: Rg1.1, U1.8 (IO15)
VLV_MED: Rg2.1, U1.9 (IO16)

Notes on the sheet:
POWER: 24V in -> 5V buck -> 3V3 LDO
ESP32-S3 MCU + PROGRAM / USB HEADER
CAN-FD: MCP2518FD + TJA1051 xcvr
FLUSH SOLENOID DRIVERS (low-side N-FET)
PUMP / CHILLER / DEIONISER (SSR drive)
ANALOG + DIGITAL SENSORS

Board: 4 copper layers, 61 parts (0 on the bottom side), 51 nets, no tracks yet.

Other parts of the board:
MH1, MH2, MH3, MH4: M3; MountingHole_3.2mm_M3

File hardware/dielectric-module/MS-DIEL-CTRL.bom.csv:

qty,value,footprint,refs
6,100R,R_0805_2012Metric,Rb4 Rb5 Rb6 Rg1 Rg2 Rg3
4,100nF,C_0805_2012Metric,C1 C10 C4 C9
6,10k,R_0805_2012Metric,R1 R2 R8 Rc1 Rl1 Rp1
3,10uF,C_0805_2012Metric,C2 C7 C8
1,10uH,L_7.3x7.3_H3.5,L1
1,120R,R_0805_2012Metric,R3
2,18pF,C_0805_2012Metric,C11 C12
3,1N4007,D_SMA,D1 D2 D3
1,1uF,C_0805_2012Metric,C3
3,20k,R_0805_2012Metric,Rc2 Rl2 Rp2
2,22uF,C_0805_2012Metric,C5 C6
1,24V_IN,"TerminalBlock_Phoenix_MPT-0,5-2-2.54_1x02_P2.54mm_Horizontal",J1
1,40MHz,Crystal_SMD_3215-2Pin_3.2x1.5mm,Y1
1,4k7,R_0805_2012Metric,R4
1,75k,R_0805_2012Metric,R7
1,AMS1117-3.3,SOT-223-3_TabPin2,U5
1,ANALOG_SENSORS,JST_XH_B6B-XH-A_1x06_P2.50mm_Vertical,J5
6,AO3400A,SOT-23,Q1 Q2 Q3 Q4 Q5 Q6
1,AO3401A,SOT-23,Q7
1,AP3402,SOT-23-6,U4
1,B340,D_SMA,D6
1,CAN,"TerminalBlock_Phoenix_MPT-0,5-3-2.54_1x03_P2.54mm_Horizontal",J2
1,ESP32-S3-WROOM-1,ESP32-S3-WROOM-1,U1
1,FLOW_FLOATS,JST_XH_B6B-XH-A_1x06_P2.50mm_Vertical,J7
1,FLUSH_SOL,"TerminalBlock_Phoenix_MPT-0,5-6-2.54_1x06_P2.54mm_Horizontal",J3
4,M3,MountingHole_3.2mm_M3,MH1 MH2 MH3 MH4
1,MCP2518FD,SOIC-14_3.9x8.7mm_P1.27mm,U2
1,PROG_USB,PinHeader_1x06_P2.54mm_Vertical,J8
1,PUMP_CHILL_DEION,"TerminalBlock_Phoenix_MPT-0,5-6-2.54_1x06_P2.54mm_Horizontal",J4
1,SMBJ24A,D_SMA,D5
1,TEMP_1WIRE,JST_XH_B4B-XH-A_1x04_P2.50mm_Vertical,J6
1,TJA1051T-3,SOIC-8_3.9x4.9mm_P1.27mm,U3

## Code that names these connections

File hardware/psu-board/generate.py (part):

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net("HV-", ("U12", "3"))                                       # voltage-amp VINN ref to HV-

# ---- isolation barrier, LOGIC side ----
net("GATE_PWM", P("U1", "PA8"), ("U10", "1"))                  # STM32 HRTIM -> UCC21520 INA
net("ISENSE_P", ("U11", "7"), P("U1", "PA0")); net("ISENSE_N", ("U11", "6"), P("U1", "PA1"))
net("VSENSE_P", ("U12", "7"), P("U1", "PA2")); net("VSENSE_N", ("U12", "6"), P("U1", "PA3"))
net("DIO_TX", P("U1", "PB12"), ("U13", "3")); net("DIO_RX", P("U1", "PB13"), ("U13", "14"))

# ---- isolated supplies (DEFERRED isolated DC-DC; [REVIEW]) ----
net("GDRV_VDD", ("U10", "16"))                                 # UCC21520 VDDA - isolated +gate supply
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    P("Y1", "2"), P("Y1", "4"), P("D1", "1"), P("D2", "1"))

# ---- STM32 housekeeping ----
net("OSC_IN", P("U1", "PF0"), P("Y1", "1")); net("OSC_OUT", P("U1", "PF1"), P("Y1", "3"))
net("SWDIO", P("U1", "PA13"), P("J5", "2")); net("SWCLK", P("U1", "PA14"), P("J5", "4"))
net("NRST", P("U1", "PG10"), P("J5", "5"))            # PG10/NRST shared on LQFP48 [REVIEW]
net("FDCAN_TX", P("U1", "PB9"), P("U2", "TXD")); net("FDCAN_RX", P("U1", "PB8"), P("U2", "RXD"))
net("NTC_AIN", P("U1", "PA4"), P("J6", "1"))
net("RUN", P("U1", "PB0"), P("R4", "1")); net("RUN_LED", P("R4", "2"), P("D1", "2"))
net("FAULT", P("U1", "PB1"), P("R5", "1")); net("FAULT_LED", P("R5", "2"), P("D2", "2"))
# ---- CAN bus ----
net("CANH", P("U2", "CANH"), P("R3", "1"), P("J3", "1"))
net("CANL", P("U2", "CANL"), P("R3", "2"), P("J3", "2"))
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
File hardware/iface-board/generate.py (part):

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# ----------------------------- parts -----------------------------
# PiBot interface headers (pin headers; flying leads to the PiBot's SPI header + screw terminals)
part("J1", "TO_PIBOT", "Connector_Generic", "Conn_01x08", "Connector_PinHeader_2.54mm",
     "PinHeader_1x08_P2.54mm_Vertical", 10, 16)            # SCK,MOSI,MISO,MCP_CS,MCP_INT,+3V3,+5V,GND
part("J2", "TO_PIBOT_BC", "Connector_Generic", "Conn_01x03", "Connector_PinHeader_2.54mm",
     "PinHeader_1x03_P2.54mm_Vertical", 10, 44)            # HX_SCK(gpio33),HX_DOUT(gpio32),GND
Cc("C1", "10uF", 24, 12)   # +3V3 bulk
Cc("C2", "10uF", 24, 48)   # +5V bulk
part("D2", "PWR", "Device", "LED", "LED_SMD", "LED_0805_2012Metric", 10, 62)
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S.power_flag("+3V3", snap(20), snap(12))
S.power_flag("+5V", snap(60), snap(12))
S.power_flag("GND", snap(100), snap(12))
S.power_flag("AVDD", snap(392), snap(150))   # AVDD is regulated by Q1 (not a power-output pin)

sch_path = os.path.join(HERE, "MS-EDM-IFACE.kicad_sch")
S.write(sch_path)
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
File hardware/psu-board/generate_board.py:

"""
Generate MS-EDM-PSU.kicad_pcb — ARCHITECTURE SCAFFOLD ONLY (review, not fabrication).

  & "C:\\Program Files\\KiCad\\10.0\\bin\\python.exe" generate_board.py

HV pulse supply. Footprints are placed into an HV region (left) and an isolated logic/CAN
region (right) with a barrier gap between them. Logic/CAN side is fully netted; HV-side nets
are named for review. SiC part, snubber, isolation ratings, creepage, thermals and ALL routing
are deferred to a power engineer (see DESIGN.md). DO NOT FABRICATE OR POWER AS-IS.
"""
import os, sys
sys.path.insert(0, os.path.join(os.path.dirname(__file__), "..", "scripts"))
import pcbnew
from kizen import Board

HERE = os.path.dirname(os.path.abspath(__file__))
W, H = 150.0, 95.0
BARRIER_X = 64.0   # isolation slot / keep-out centre

b = Board(copper_layers=4)

R0805 = ("Resistor_SMD", "R_0805_2012Metric")
C0805 = ("Capacitor_SMD", "C_0805_2012Metric")
R2512 = ("Resistor_SMD", "R_2512_6332Metric")
SO8   = ("Package_SO", "SOIC-8_3.9x4.9mm_P1.27mm")
TB2 = ("TerminalBlock_Phoenix", "TerminalBlock_Phoenix_MPT-0,5-2-2.54_1x02_P2.54mm_Horizontal")  # PLACEHOLDER; HV/gap need uprated terminals
TB3 = ("TerminalBlock_Phoenix", "TerminalBlock_Phoenix_MPT-0,5-3-2.54_1x03_P2.54mm_Horizontal")

def C(ref, lib_fp, x, y, val="", rot=0):
    b.add(ref, val, lib_fp[0], lib_fp[1], x, y, rot)

# ============================ HV POWER REGION (left) ============================
C("J1", TB2, 12, 18, "HV_DC_IN__60-120V")                         # external isolated bus
C("F1", R2512, 22, 14, "FUSE_placeholder")
C("D10", ("Diode_SMD", "D_SMC"), 18, 26, "HV_TVS")
C("C20", ("Capacitor_THT", "CP_Radial_D10.0mm_P5.00mm"), 30, 20, "bulk_220uF")
C("C21", ("Capacitor_THT", "CP_Radial_D10.0mm_P5.00mm"), 40, 20, "bulk_220uF")
C("C22", R2512, 50, 16, "film_1uF")                               # film cap (placeholder fp)
C("R20", R2512, 52, 26, "bleeder")
C("Q1", ("Package_TO_SOT_THT", "TO-247-3_Vertical"), 30, 44, "SiC_MOSFET")
C("Rg10", R0805, 44, 38, "gate_R")
C("D11", ("Package_TO_SOT_THT", "TO-220-3_Vertical"), 48, 44, "SiC_freewheel")
C("R21", R2512, 56, 40, "snubber_R"); C("C23", C0805, 56, 46, "snubber_C")
C("R22", R2512, 28, 60, "shunt_R")                                # current sense
C("J2", TB2, 12, 60, "GAP_OUT__wire_work")

# ---- isolation barrier crossers (placed on the slot) ----
C("U10", ("Package_SO", "SOIC-16W_7.5x10.3mm_P1.27mm"), BARRIER_X, 40, "ISO_GATE_DRIVER")
C("U11", SO8, BARRIER_X, 58, "ISO_CURRENT_AMP")
C("U12", SO8, BARRIER_X, 70, "ISO_VOLTAGE_AMP")
C("U13", ("Package_SO", "SOIC-16_3.9x9.9mm_P1.27mm"), BARRIER_X, 24, "DIGITAL_ISOLATOR")

# ============================ LOGIC / CAN REGION (right) ========================
C("U1", ("Package_QFP", "LQFP-48_7x7mm_P0.5mm"), 95, 44, "STM32G474")
C("Y1", ("Crystal", "Crystal_SMD_3225-4Pin_3.2x2.5mm"), 80, 30, "24MHz")
C("C1", C0805, 86, 30, "100nF"); C("C2", C0805, 104, 30, "100nF")
C("C3", C0805, 86, 58, "100nF"); C("C4", C0805, 104, 58, "10uF")
C("U2", SO8, 120, 56, "TJA1051")
C("C5", C0805, 112, 56, "100nF")
C("R3", R0805, 130, 62, "120R_term")
C("J3", TB3, 134, 70, "CAN")
C("J4", TB2, 134, 18, "LOGIC_5V_IN")
C("U3", ("Package_TO_SOT_SMD", "SOT-223-3_TabPin2"), 118, 20, "AMS1117-3.3")
C("C6", C0805, 110, 26, "10uF"); C("C7", C0805, 126, 26, "10uF")
C("J5", ("Connector_PinHeader_2.54mm", "PinHeader_1x05_P2.54mm_Vertical"), 80, 62, "SWD")
C("J6", TB2, 120, 80, "NTC_TEMP")
C("D1", ("LED_SMD", "LED_0805_2012Metric"), 108, 68, "LED_RUN"); C("R4", R0805, 112, 68, "1k")
C("D2", ("LED_SMD", "LED_0805_2012Metric"), 108, 72, "LED_FAULT"); C("R5", R0805, 112, 72, "1k")

# ============================ NETS ============================
def n(net, *rp): b.bus(net, *rp)

# ---- HV-side named nets (intra-region; for review, NOT routed) ----
n("HV+", ("J1","1"), ("F1","1"))
n("HVF", ("F1","2"), ("D10","1"), ("C20","1"), ("C21","1"), ("C22","1"), ("R20","1"), ("Q1","2"))  # bus after fuse (TO-247 pin2=Drain)
n("HV-", ("J1","2"), ("D10","2"), ("C20","2"), ("C21","2"), ("C22","2"), ("R20","2"),
         ("R22","2"), ("D11","2"))
n("SW_NODE", ("Q1","1"), ("Rg10","2"), ("D11","1"), ("R21","1"), ("J2","1"))   # TO-247 pin1=Gate? see note
n("GAP_RTN", ("J2","2"), ("R22","1"))
n("GATE_DRV", ("U10","9"), ("Rg10","1"))         # isolated gate driver output (verify pinout)
n("SNUB", ("R21","2"), ("C23","1")); n("SNUB_G", ("C23","2"))
n("ISENSE_HV", ("U11","2"), ("R22","1")); n("ISENSE_HV_G", ("U11","3"), ("R22","2"))
n("VSENSE_HV", ("U12","2")); n("VSENSE_HV_G", ("U12","3"))

# ---- isolation barrier: logic-side of the crossers ----
n("GATE_PWM", ("U1","26"), ("U10","2"))          # STM32 HRTIM out -> iso gate driver in (verify)
n("ISENSE", ("U11","6"), ("U1","11"))            # iso amp out -> ADC
n("VSENSE", ("U12","6"), ("U1","12"))
n("DIO_A", ("U13","2"), ("U1","27")); n("DIO_B", ("U13","15"), ("U1","28"))   # spare iso digital

# ---- logic power ----
n("+5V", ("J4","1"), ("U3","3"), ("C6","1"), ("U2","3"), ("C5","1"))
n("+3V3", ("U3","2"), ("C7","1"), ("U1","24"), ("U1","36"), ("U1","48"), ("U1","9"),
          ("C1","1"), ("C2","1"), ("C3","1"), ("C4","1"), ("U2","5"))
n("GNDL", ("J4","2"), ("U3","1"), ("C6","2"), ("C7","2"),
          ("U1","23"), ("U1","35"), ("U1","47"), ("U1","8"),
          ("C1","2"), ("C2","2"), ("C3","2"), ("C4","2"),
          ("U2","2"), ("U2","8"), ("C5","2"), ("J5","3"),
          ("R4","2"), ("R5","2"), ("J6","2"))

# ---- STM32 housekeeping (verify STM32G474 LQFP48 pinout) ----
n("OSC_IN", ("U1","5"), ("Y1","1")); n("OSC_OUT", ("U1","6"), ("Y1","3"))
n("Y1_G", ("Y1","2"), ("Y1","4"))
n("SWDIO", ("U1","34"), ("J5","2")); n("SWCLK", ("U1","37"), ("J5","4"))
n("NRST", ("U1","7"), ("J5","5")); n("SWD_3V3", ("J5","1"))
n("FDCAN_TX", ("U1","46"), ("U2","1")); n("FDCAN_RX", ("U1","45"), ("U2","4"))
n("NTC_AIN", ("U1","14"), ("J6","1"))
n("RUN", ("U1","29"), ("D1","2")); n("RUN_R", ("D1","1"), ("R4","1"))
n("FAULT", ("U1","30"), ("D2","2")); n("FAULT_R", ("D2","1"), ("R5","1"))

# ---- CAN bus ----
n("CANH", ("U2","7"), ("R3","1"), ("J3","1"))
n("CANL", ("U2","6"), ("R3","2"), ("J3","2"))
n("CAN_GND", ("J3","3"))

# ============================ OUTLINE / BARRIER / ZONES ============================
b.rect_outline(W, H, 0, 0, r=3.0)
# isolation slot: a milled gap is drawn on Edge.Cuts as two short segments (visual marker;
# a real isolation slot/route is a layout decision). Mark with silk too.
b._seg((BARRIER_X, 6), (BARRIER_X, 30))
b._seg((BARRIER_X, 50), (BARRIER_X, H - 6))
# HV ground pour (left of barrier) and logic ground pour (right of barrier)
b.gnd_zone(pcbnew.B_Cu, BARRIER_X - 8, H - 4, 2, 2, "HV-")
b.gnd_zone(pcbnew.B_Cu, W - (BARRIER_X + 8) - 2, H - 4, BARRIER_X + 8, 2, "GNDL")
b.gnd_zone(pcbnew.In2_Cu, W - (BARRIER_X + 8) - 2, H - 4, BARRIER_X + 8, 2, "GNDL")
for (mx, my) in [(5, 5), (W - 5, 5), (5, H - 5), (W - 5, H - 5)]:
    b.mounting_hole(mx, my, "GNDL")
b.fill_zones()

pcb_path = os.path.join(HERE, "MS-EDM-PSU.kicad_pcb")
ok = b.save(pcb_path)
b.write_netlist_csv(os.path.join(HERE, "MS-EDM-PSU.netlist.csv"))
b.write_bom_csv(os.path.join(HERE, "MS-EDM-PSU.bom.csv"))
print("saved:", ok, pcb_path)
print(b.summary())
